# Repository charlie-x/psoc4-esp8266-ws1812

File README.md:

psoc4-esp8266-ws1812
====================

PSOC 4 with ESP8266 for WS2812B LED Strips

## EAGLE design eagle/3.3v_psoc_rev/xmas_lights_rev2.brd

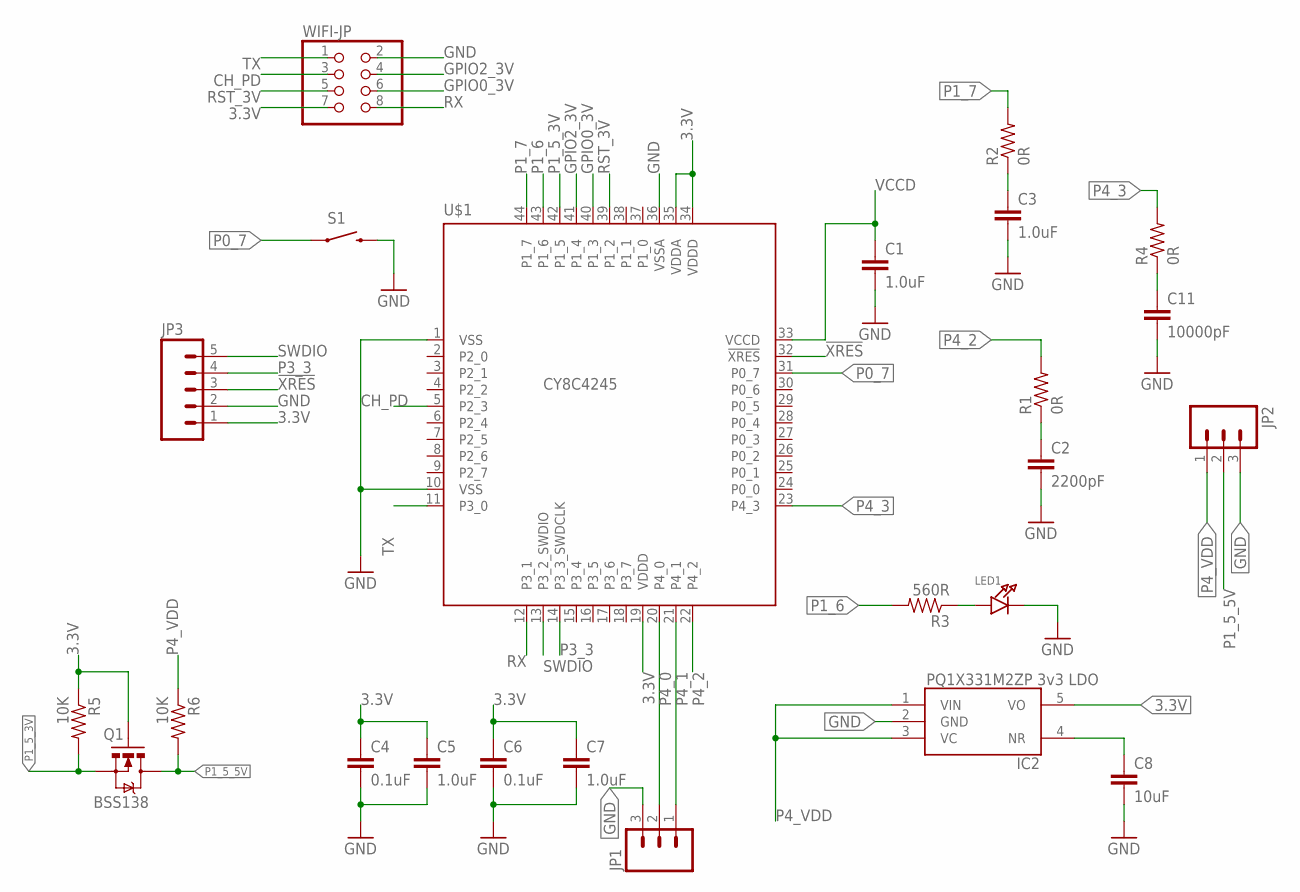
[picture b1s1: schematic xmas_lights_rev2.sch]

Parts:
C1, C3, C5, C7: 1.0uF; 0805
C2: 2200pF; 0805
C4, C6: 0.1uF; 0805
C8: 10uF; 0805
C11: 10000pF; 0805
IC2: PQ1X331M2ZP-3V3-LDO-SOT-23-5; SOT-23-5
JP1, JP2: M031X03_NO_SILK; 1X03_NO_SILK
JP3: M05PTH; 1X05
LED1: LED0805; CHIPLED_0805
Q1: BSS138; SOT23-3
R1, R2, R4: 0R; 0805
R3: 560R; 0805
R5, R6: 10K; 0805
S1: SPARKFUN_SWITCH-MOMENTARY-2SMD; SPARKFUN_TACTILE_SWITCH_SMD
U$1: CY8C4245; TQFP44
WIFI-JP: PINHD-2X4; 2X04

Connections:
3.3V: C4.1, C5.1, C6.1, C7.1, IC2.5 (VO), JP3.1, Q1.1 (G), R5.1, U$1.19 (VDDD), U$1.34 (VDDD), U$1.35 (VDDA), WIFI-JP.7
!XRES: JP3.3, U$1.32 (!XRES)
CH_PD: U$1.5 (P2_3), WIFI-JP.3
GND: C1.2, C2.2, C3.2, C4.2, C5.2, C6.2, C7.2, C8.2, C11.2, IC2.2 (GND), JP1.3, JP2.3, JP3.2, LED1.C, S1.3 (2), U$1.1 (VSS), U$1.10 (VSS), U$1.36 (VSSA), WIFI-JP.2
GPIO0_3V: U$1.40 (P1_3), WIFI-JP.6
GPIO2_3V: U$1.41 (P1_4), WIFI-JP.4
unnamed: C2.1, R1.1
unnamed: C3.1, R2.1
unnamed: C11.1, R4.1
unnamed: LED1.A, R3.1
unnamed: C8.1, IC2.4 (NR)
P0_7: S1.1, U$1.31 (P0_7)
P1_5_3V: Q1.2 (S), R5.2, U$1.42 (P1_5)
P1_5_5V: JP2.2, Q1.3 (D), R6.2
P1_6: R3.2, U$1.43 (P1_6)
P1_7: R2.2, U$1.44 (P1_7)
P3_3: JP3.4, U$1.14 (P3_3_SWDCLK)
P4_0: JP1.2, U$1.20 (P4_0)
P4_1: JP1.1, U$1.21 (P4_1)
P4_2: R1.2, U$1.22 (P4_2)
P4_3: R4.2, U$1.23 (P4_3)
P4_VDD: IC2.1 (VIN), IC2.3 (VC), JP2.1, R6.1
RST_3V: U$1.39 (P1_2), WIFI-JP.5
RX: U$1.12 (P3_1), WIFI-JP.8
SWDIO: JP3.5, U$1.13 (P3_2_SWDIO)
TX: U$1.11 (P3_0), WIFI-JP.1
VCCD: C1.1, U$1.33 (VCCD)

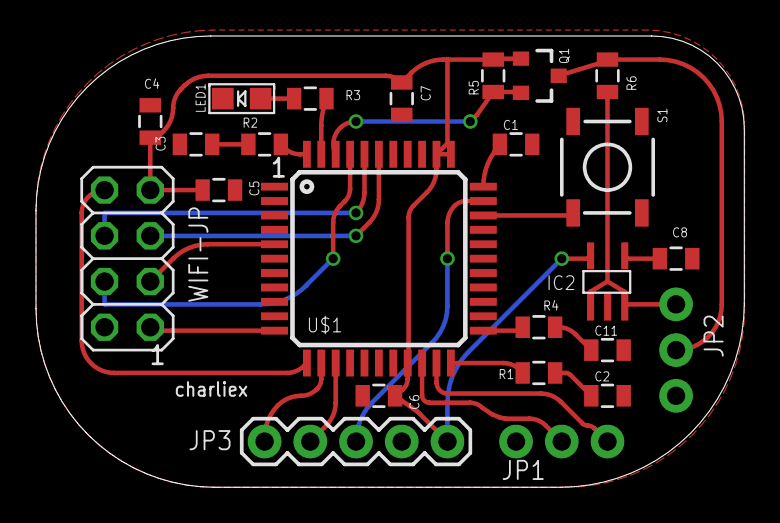
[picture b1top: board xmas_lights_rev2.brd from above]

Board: 2 copper layers, 39.4 x 25.1 mm, 24 parts (0 on the bottom side), 27 nets.

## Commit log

2014-12-07 initial checkin of revision 1 board
2014-12-23 added firmware code
2014-12-24 RGB offsets all match again..
2014-12-24 simple udp test client
2014-12-24 added osx/linux simple udp test send.
2014-12-24 adding 3.3v version of board, this has all running at 3.3v with a logic level convertor to 5v for the led. untested, gerber zip file that i submitted to the pcb house today is also included.
2014-12-25 this is a very silly app, if you're sending out from the lights server as broadcast UDP, it'll listen and display what the lights are displaying.
    WIFI UDP broadcast is a terrible idea, and this app abuses MFC's OnPaint. Its just a bit of fun though.
2014-12-25 slightly neater layout
2014-12-25 Slightly less awful way of forcing an invalidate, but not really.
2014-12-25 fixed rgb layout(again)
2014-12-25 added an ontimer for udp recv and gui refresh.

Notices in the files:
parts and their libraries:
SparkFun-Capacitors: Licensing: CC v3.0 Share-Alike You are welcome to use this library for commercial purposes.
microbuilder: This work is placed in the public domain, and may be freely used for commercial and non-commercial work with the following conditions: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
